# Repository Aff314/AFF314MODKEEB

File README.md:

# AFF314MODKEEB
AFF314MODKEEB is a 4x12 lowprofile keyboard. What makes it special are its modules. You can attach modules on top or on the right side which are connected with are then connected by magnets.

I had the idea because I daily drive 40% and 75% keyboards. I wanted to have one keyboard which can be used for both. With this keyboard you can have a full sized keyboard with number-keys, f-keys and arrow keys if you need it for a game or programm. But if you want to have a more minimal keyboard you can just detach the modules and have a nice and compact 40% keyboard. 

## Modules
You can attach the modules on top and on the right side.
So far I have designed three modules.

One for the right side. It has arrow-keys plus six extra keys that can be used for what ever you like.

The two that go on top are either a number or f-key row or a number plus f-key module. I decided to only order the pcbs for the number plus f-key module since you can type the numbers and f-keys also with layers so when I really need the f-keys or numbers the others don't hurt and it would take away from that convenience I wanted if you have so many modules laying around.

If you want to you can design your own modules. You can use the same cases I designed and you have to modify the [pcbs](./pcb).

## Building
If you want to build the keyboard you have to not only solder on the pcb but also solder some wires. Once the keyboard is built I will add pictures for better understanding.

### Flashing
To flash the firmware you have to download the [UF2 file](./firmware/firmware.uf2).

### PCB
On the pcbs you first have to solder on all the diodes and hotswap sockets. Then you can solder on the power switch if you want to use one, because you can also use it without a powerswitch and solder the battery directly or just use it wired.

### Connectors
Before we wire everything we need the prepare the connectors. For this you need to print the [mounting bracktets](./3d). Then you can melt the heat inserts in the mounting bracket and attach it to the magnetic connector.

### Case
We also need to prepare the case. This is pretty straight forward as you only need to add the heat inserts.

### Wiring
We will start with the magnetic connectors we have prepared. We need to wire the cables to the pins. It is probably a good idea to use heat shrink tubing to isolate the exposed pins right by eachother but you dont have to. Once the wires are soldered to them we take them and mount them inside the case.
Look at the [schematics](./pics) and at the [wiring_guides](./pics) for help.

You can wire them to the mcu now. You also need to wire the rows and columns from the pcb to the mcu. For this you can take a look at the pcb but I will also add pictures once it's build.
At last you can wire the battery.

### MCU
The nice nano or if built wired the rp2040 will fit perfectly in the cutout for it in the bottom of the case. Optionaly you could glue it in place but it will also hold on its own so there is no need fo it unless you want the most secure fit.

## Fallout
I made this keyboard for fallout from hackclub and they give the chance for you to show off your project in a magazine. This is my page for zine. I will change it once I've built it irl because the real pictures would make it look way better.

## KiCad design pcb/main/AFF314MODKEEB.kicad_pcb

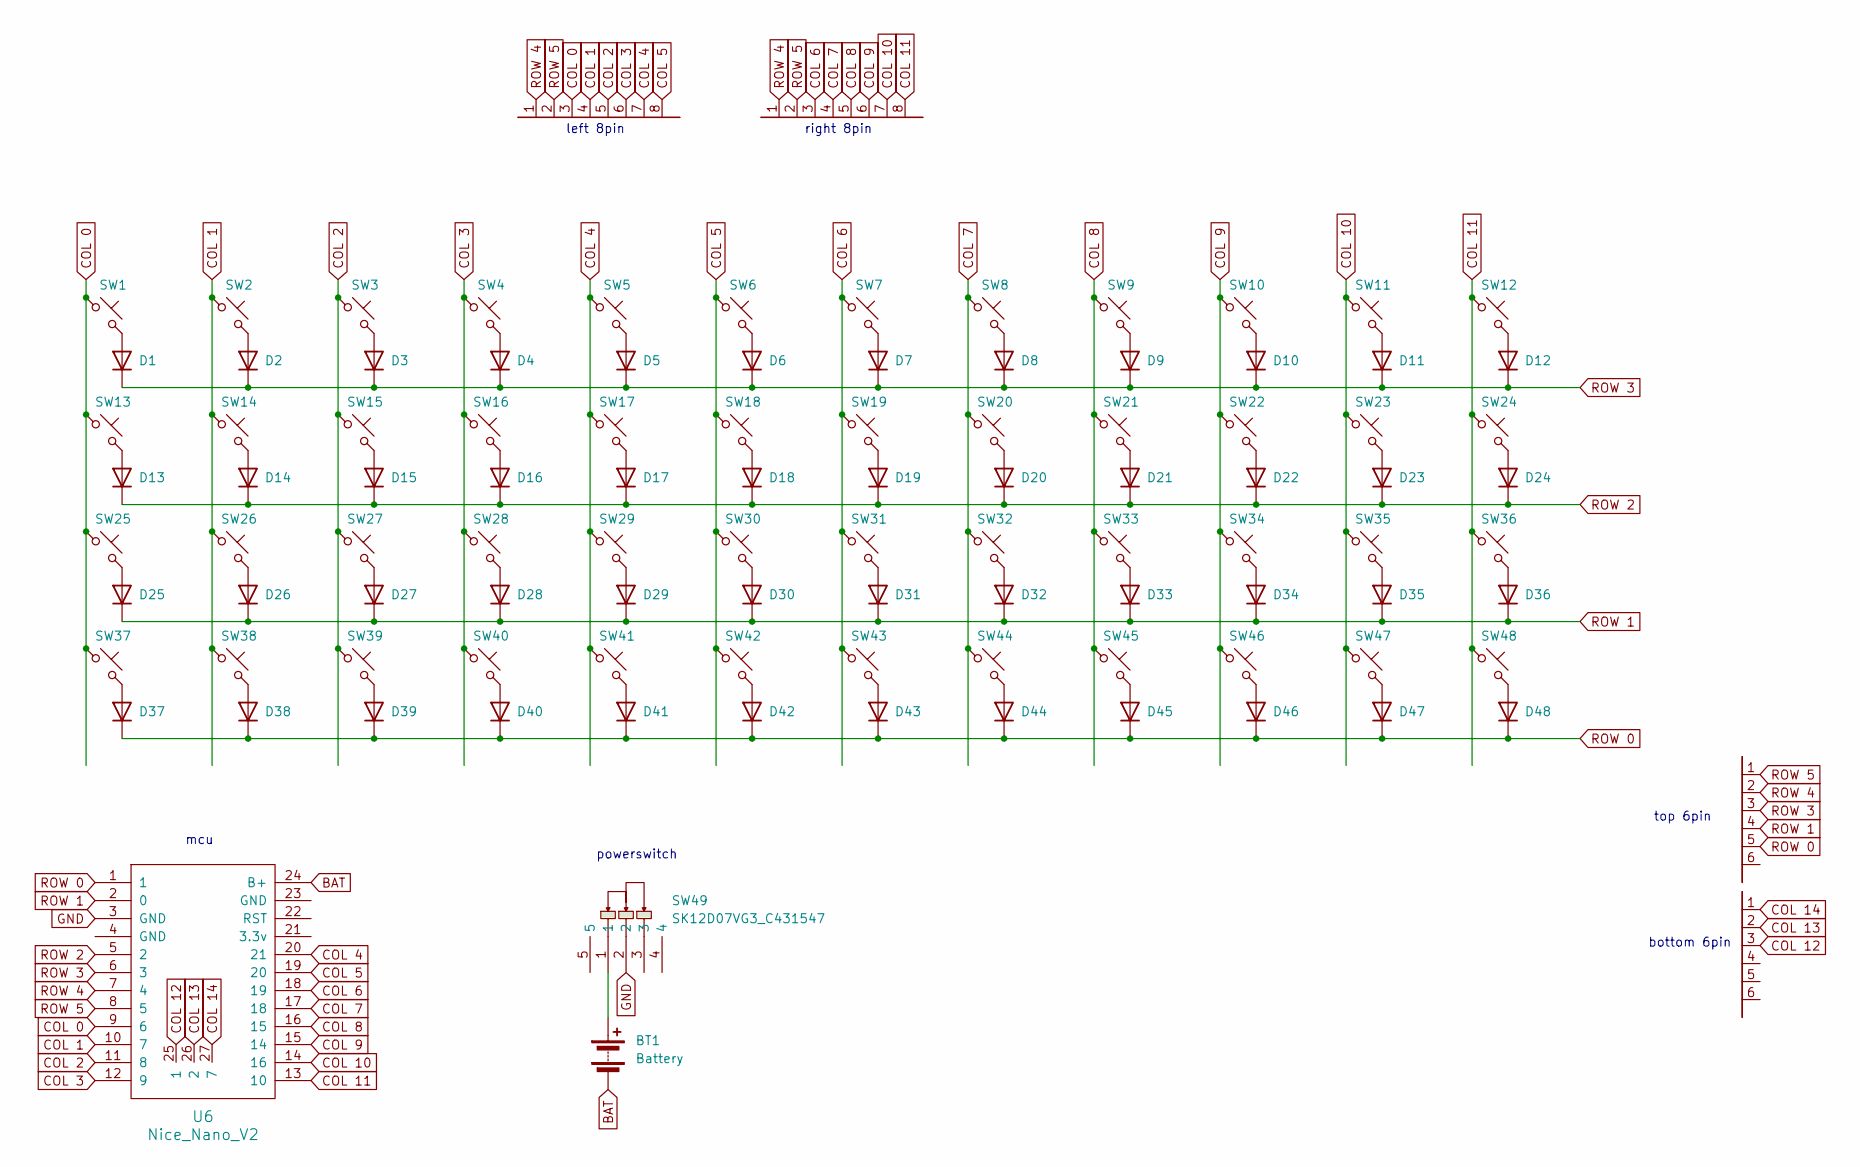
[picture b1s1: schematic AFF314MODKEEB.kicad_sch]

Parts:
BT1: Battery
D1, D2, D3, D4, D5, D6, D7, D8, D9, D10, D11, D12, D13, D14, D15, D16, D17, D18, D19, D20, D21, D22, D23, D24, D25, D26, D27, D28, D29, D30, D31, D32, D33, D34, D35, D36, D37, D38, D39, D40, D41, D42, D43, D44, D45, D46, D47, D48: D; Diode_SOD123
SW1, SW2, SW3, SW4, SW5, SW6, SW7, SW8, SW9, SW10, SW11, SW12, SW13, SW14, SW15, SW16, SW17, SW18, SW19, SW20, SW21, SW22, SW23, SW24, SW25, SW26, SW27, SW28, SW29, SW30, SW31, SW32, SW33, SW34, SW35, SW36, SW37, SW38, SW39, SW40, SW41, SW42, SW43, SW44, SW45, SW46, SW47, SW48: SW_Push_45deg; choc_16
SW49: SK12D07VG3_C431547; SW-TH_SK12D07VG3; MPN SK12D07VG3; LCSC Part C431547
U2, U3, U5, U7: (no value)
U6: Nice_Nano_V2

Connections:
COL 0: SW1.1, SW13.1, SW25.1, SW37.1, U5.3, U6.9 (6)
COL 1: SW2.1, SW14.1, SW26.1, SW38.1, U5.4, U6.10 (7)
COL 2: SW3.1, SW15.1, SW27.1, SW39.1, U5.5, U6.11 (8)
COL 3: SW4.1, SW16.1, SW28.1, SW40.1, U5.6, U6.12 (9)
COL 4: SW5.1, SW17.1, SW29.1, SW41.1, U5.7, U6.20 (21)
COL 5: SW6.1, SW18.1, SW30.1, SW42.1, U5.8, U6.19 (20)
COL 6: SW7.1, SW19.1, SW31.1, SW43.1, U6.18 (19), U7.3
COL 7: SW8.1, SW20.1, SW32.1, SW44.1, U6.17 (18), U7.4
COL 8: SW9.1, SW21.1, SW33.1, SW45.1, U6.16 (15), U7.5
COL 9: SW10.1, SW22.1, SW34.1, SW46.1, U6.15 (14), U7.6
COL 10: SW11.1, SW23.1, SW35.1, SW47.1, U6.14 (16), U7.7
COL 11: SW12.1, SW24.1, SW36.1, SW48.1, U6.13 (10), U7.8
unnamed: BT1.1 (+), SW49.1
unnamed: BT1.2 (-), U6.24 (B+)
unnamed: D1.2 (A), SW1.2
unnamed: D2.2 (A), SW2.2
unnamed: D3.2 (A), SW3.2
unnamed: D4.2 (A), SW4.2
unnamed: D5.2 (A), SW5.2
unnamed: D6.2 (A), SW6.2
unnamed: D7.2 (A), SW7.2
unnamed: D8.2 (A), SW8.2
unnamed: D9.2 (A), SW9.2
unnamed: D10.2 (A), SW10.2
unnamed: D11.2 (A), SW11.2
unnamed: D12.2 (A), SW12.2
unnamed: D13.2 (A), SW13.2
unnamed: D14.2 (A), SW14.2
unnamed: D15.2 (A), SW15.2
unnamed: D16.2 (A), SW16.2
unnamed: D17.2 (A), SW17.2
unnamed: D18.2 (A), SW18.2
unnamed: D19.2 (A), SW19.2
unnamed: D20.2 (A), SW20.2
unnamed: D21.2 (A), SW21.2
unnamed: D22.2 (A), SW22.2
unnamed: D23.2 (A), SW23.2
unnamed: D24.2 (A), SW24.2
unnamed: D25.2 (A), SW25.2
unnamed: D26.2 (A), SW26.2
unnamed: D27.2 (A), SW27.2
unnamed: D28.2 (A), SW28.2
unnamed: D29.2 (A), SW29.2
unnamed: D30.2 (A), SW30.2
unnamed: D31.2 (A), SW31.2
unnamed: D32.2 (A), SW32.2
unnamed: D33.2 (A), SW33.2
unnamed: D34.2 (A), SW34.2
unnamed: D35.2 (A), SW35.2
unnamed: D36.2 (A), SW36.2
unnamed: D37.2 (A), SW37.2
unnamed: D38.2 (A), SW38.2
unnamed: D39.2 (A), SW39.2
unnamed: D40.2 (A), SW40.2
unnamed: D41.2 (A), SW41.2
unnamed: D42.2 (A), SW42.2
unnamed: D43.2 (A), SW43.2
unnamed: D44.2 (A), SW44.2
unnamed: D45.2 (A), SW45.2
unnamed: D46.2 (A), SW46.2
unnamed: D47.2 (A), SW47.2
unnamed: D48.2 (A), SW48.2
unnamed: U2.1, U5.2, U6.8 (5), U7.2
unnamed: U2.2, U5.1, U6.7 (4), U7.1
unnamed: U3.1, U6.27 (7)
unnamed: U3.2, U6.26 (2)
unnamed: U3.3, U6.25 (1)
unnamed: SW49.2, U6.3 (GND)
ROW 0: D37.1 (K), D38.1 (K), D39.1 (K), D40.1 (K), D41.1 (K), D42.1 (K), D43.1 (K), D44.1 (K), D45.1 (K), D46.1 (K), D47.1 (K), D48.1 (K), U2.5, U6.1
ROW 1: D25.1 (K), D26.1 (K), D27.1 (K), D28.1 (K), D29.1 (K), D30.1 (K), D31.1 (K), D32.1 (K), D33.1 (K), D34.1 (K), D35.1 (K), D36.1 (K), U2.4, U6.2 (0)
ROW 2: D13.1 (K), D14.1 (K), D15.1 (K), D16.1 (K), D17.1 (K), D18.1 (K), D19.1 (K), D20.1 (K), D21.1 (K), D22.1 (K), D23.1 (K), D24.1 (K), U6.5 (2)
ROW 3: D1.1 (K), D2.1 (K), D3.1 (K), D4.1 (K), D5.1 (K), D6.1 (K), D7.1 (K), D8.1 (K), D9.1 (K), D10.1 (K), D11.1 (K), D12.1 (K), U2.3, U6.6 (3)

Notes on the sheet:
right 8pin
powerswitch
top 6pin
bottom 6pin
left 8pin
mcu

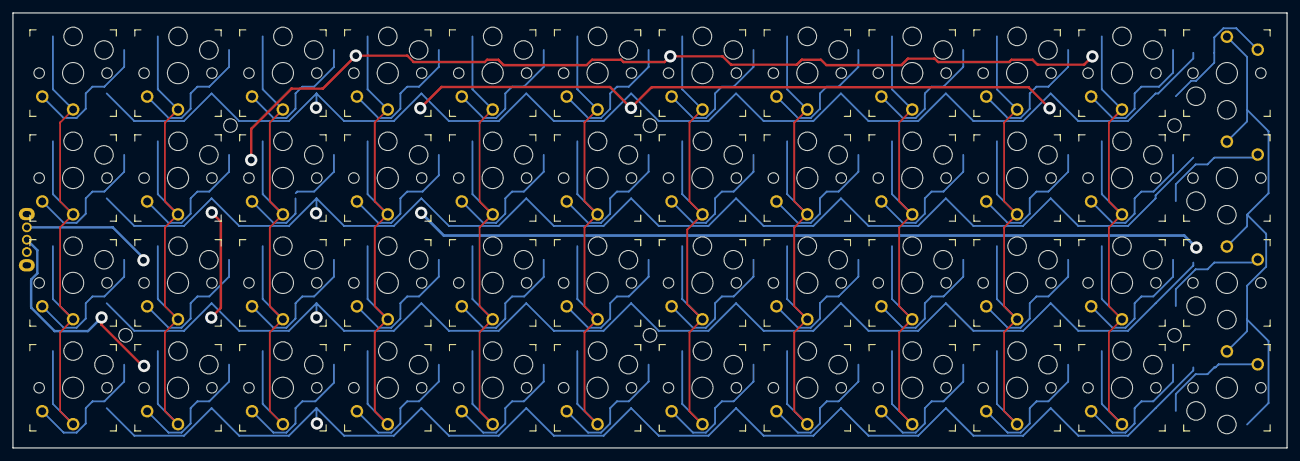
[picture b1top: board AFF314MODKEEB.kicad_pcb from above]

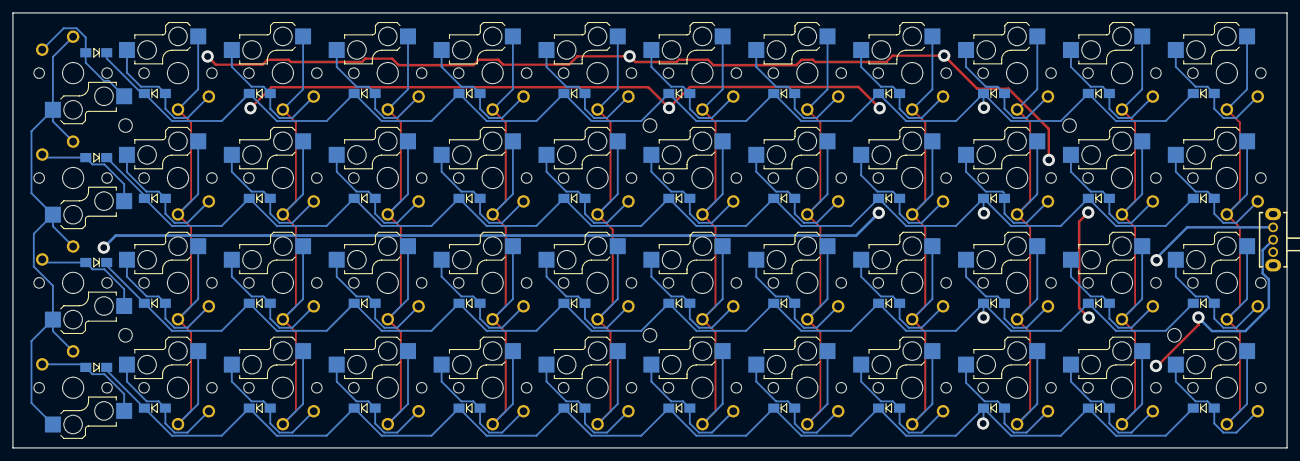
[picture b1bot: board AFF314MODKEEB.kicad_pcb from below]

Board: 2 copper layers, 206.5 x 70.5 mm, 97 parts (49 on the bottom side), 64 nets.

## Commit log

2026-06-07 Fix header formatting in README.md
2026-06-08 add pcb and 3d
2026-06-08 Add BOM CSV file for keyswitch components
2026-06-10 Add parts to BOM
2026-06-10 add pics
2026-06-10 rename images
2026-06-10 update pcb & add firmware
2026-06-10 Add wire details and update BOM entries
2026-06-10 Update wiring instructions in README
    Added references to schematics and wiring guides for clarity.
2026-06-12 add library
2026-06-12 add zine page
2026-06-12 add zine part
2026-06-12 Rename ZINE MODKEEB.pdf to ZINE_MODKEEB.pdf
2026-06-12 Rename ZINE MODKEEB.png to ZINE_MODKEEB.png
2026-06-13 zine update
2026-06-13 rename folder
2026-06-13 Format BOM.csv for consistency and clarity
